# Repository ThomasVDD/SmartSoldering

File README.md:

# SmartSoldering
SmartSoldering - Weller compatible soldering station

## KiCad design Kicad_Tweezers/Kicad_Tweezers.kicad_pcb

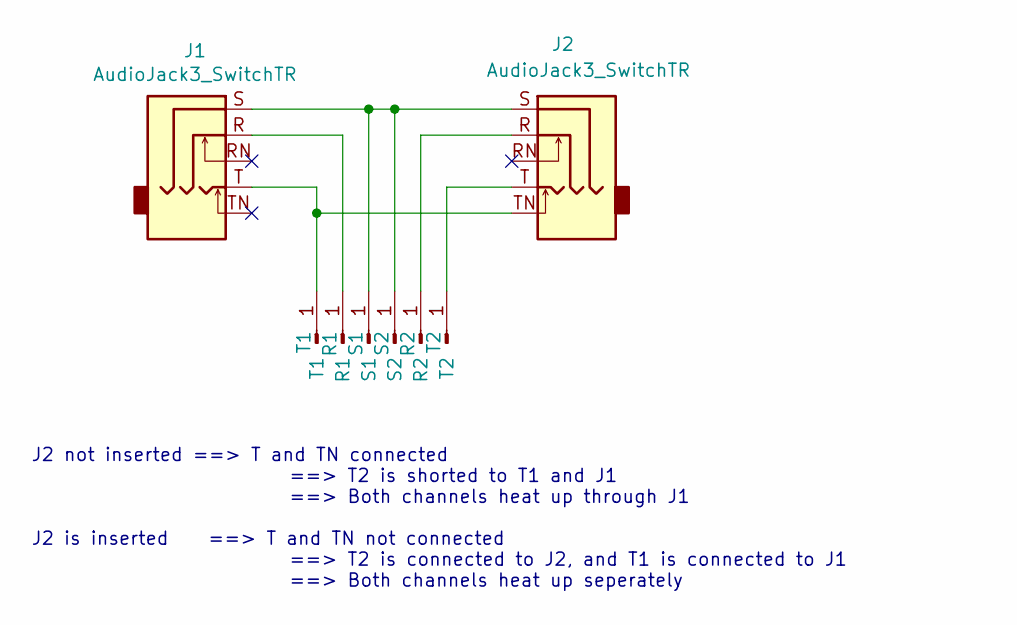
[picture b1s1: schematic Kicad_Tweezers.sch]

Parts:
J1, J2: AudioJack3_SwitchTR; Audiojack3_SwitchTR
R1: R1; Audiojack_pad
R2: R2; Audiojack_pad
S1: S1; Audiojack_pad
S2: S2; Audiojack_pad
T1: T1; Audiojack_pad
T2: T2; Audiojack_pad

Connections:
unnamed: J1.R, R1.1
unnamed: J1.S, J2.S, S1.1, S2.1
unnamed: J1.T, J2.TN, T1.1
unnamed: J2.R, R2.1
unnamed: J2.T, T2.1

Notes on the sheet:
J2 not inserted ==> T and TN connected ==> T2 is shorted to T1 and J1 ==> Both channels heat up through J1 J2 is inserted ==> T and TN not connected ==> T2 is connected to J2, and T1 is connected to J1 ==> Both channels heat up seperately

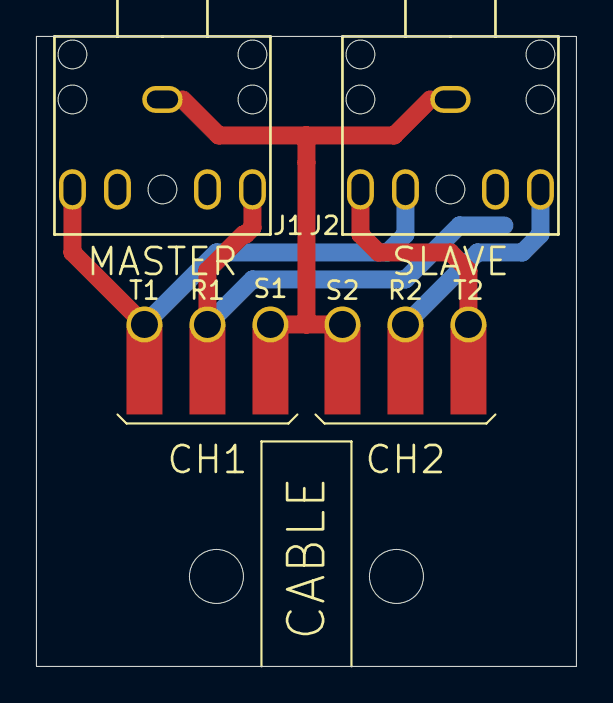
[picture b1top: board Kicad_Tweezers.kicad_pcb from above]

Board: 2 copper layers, 30.0 x 35.0 mm, 8 parts (0 on the bottom side), 5 nets.

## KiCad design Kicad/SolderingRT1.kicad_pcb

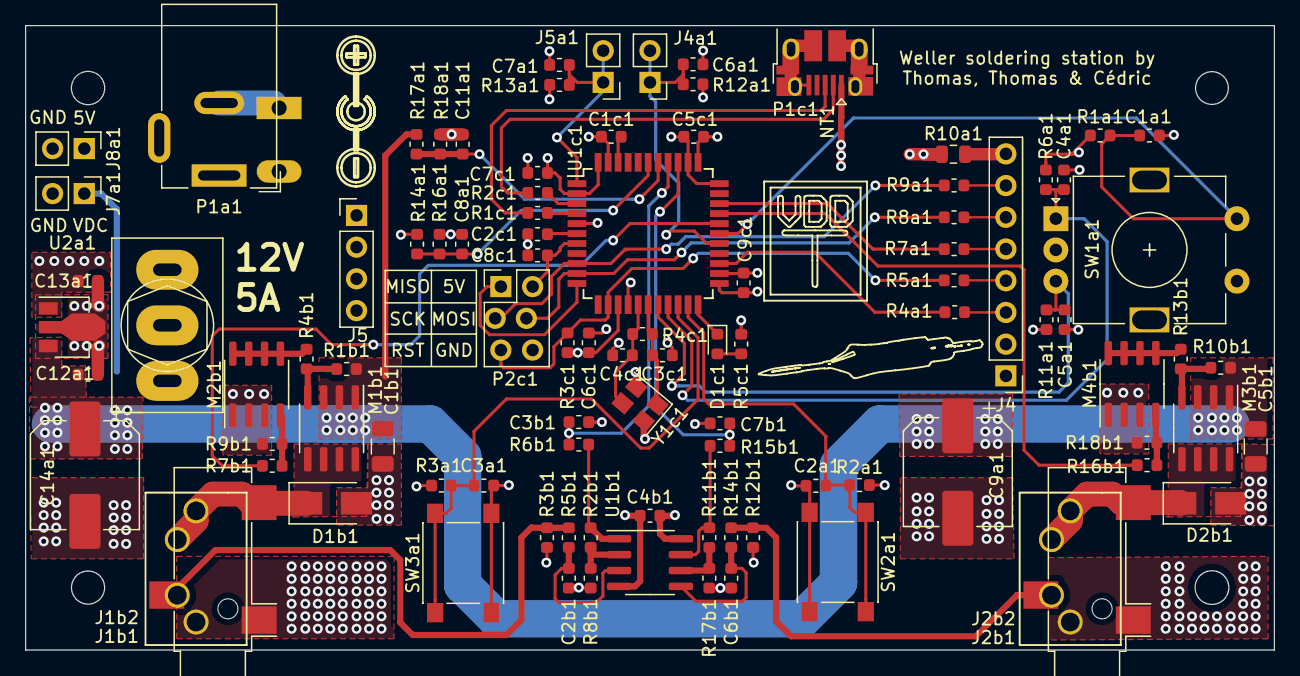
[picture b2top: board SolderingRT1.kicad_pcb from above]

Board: 4 copper layers, 100.0 x 50.0 mm, 99 parts (1 on the bottom side), 56 nets.

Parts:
C1a1, C2a1, C2b1, C3a1, C3b1, C4a1, C5a1, C6a1, C6b1, C7a1, C7b1, C8a1, C11a1: 10nF; C_0603_1608Metric
C1b1, C5b1: 10uF; C_1206_3216Metric
C1c1, C4b1, C5c1, C6c1, C7c1, C8c1, C9c1: 100nF; C_0603_1608Metric
C2c1, C12a1, C13a1: 1uF; C_0603_1608Metric
C3c1, C4c1: 22pF; C_0603_1608Metric
C9a1, C14a1: 330uF; CP_Elec_8x10.5
D1b1, D2b1: SS14; D_SMA
D1c1: LED; LED_0603_1608Metric
J1: Screw_Terminal_01x02; PhoenixContact_MC-G_02x5.08mm_Angled
J1b1, J2b1: AudioJack3; Jack_3.5mm_CUI_SJ-3523-SMT_Horizontal
J1b2, J2b2: AudioJack3; Audiojack_straight
J4: Conn_01x08_Female; PinHeader_1x08_P2.54mm_Vertical
J4a1, J5a1, J7a1, J8a1: Conn_01x02_Male; PinHeader_1x02_P2.54mm_Vertical
J5: Conn_01x04_Female; PinHeader_1x04_P2.54mm_Vertical
M1b1, M3b1: AO4407A; SOIC-8_3.9x4.9mm_P1.27mm
M2b1, M4b1: AOSP36326C; SOIC-8_3.9x4.9mm_P1.27mm
NT1: Net-Tie_2; NetTie-2_SMD_Pad0.5mm
P1a1: Barrel_Jack_Switch; BarrelJack_Wuerth_6941xx301002
P1c1: USB_B_Micro; USB_Micro-B_Amphenol_10103594-0001LF_Horizontal
P2c1: Conn_02x03_Odd_Even; PinHeader_2x03_P2.54mm_Vertical
R1a1, R2a1, R3a1, R3c1, R6a1, R9b1, R11a1, R12a1, R13a1, R17a1, R18b1: 10k; R_0603_1608Metric
R1b1, R5c1, R10b1: 2k4; R_0603_1608Metric
R1c1, R2c1: 22; R_0603_1608Metric
R2b1, R11b1: 56k; R_0603_1608Metric
R3b1, R4c1, R12b1: 1M; R_0603_1608Metric
R4a1, R4b1, R5a1, R5b1, R6b1, R7a1, R7b1, R8a1, R9a1, R13b1, R14b1, R15b1, R16b1, R18a1: 1k; R_0603_1608Metric
R8b1, R17b1: 100; R_0603_1608Metric
R10a1: 150; R_0805_2012Metric
R14a1, R16a1: 100k; R_0603_1608Metric
SW1a1: Rotary_Encoder_Switch; RotaryEncoder_Alps_EC11E-Switch_Vertical_H20mm
SW2a1, SW3a1: SW_Push; SW_Push_1P1T_NO_6x6mm_H9.5mm
SW4a1: SW_SPDT; SW_Toggle_Blue_wSlots
U1b1: OPA2335; SOIC-8_3.9x4.9mm_P1.27mm
U1c1: ATmega32U4-AU; TQFP-44_10x10mm_P0.8mm
U2a1: L78L05_SOT89; SOT-89-3
Y1c1: 16MHz; Crystal_SMD_3225-4Pin_3.2x2.5mm

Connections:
+5V: C4b1.1, C5c1.1, C6c1.1, C7c1.1, C8c1.1, C9c1.1, C13a1.1, J4.1, J8a1.1, NT1.2, P2c1.2, R1a1.2, R2a1.2, R3a1.2, R3b1.2, R3c1.2, R5c1.2, R6a1.2, R10a1.1, R11a1.2, R12a1.2, R12b1.2, R13a1.2, R14a1.2, U1b1.8, U1c1.2, U1c1.7, U1c1.14, U1c1.24, U1c1.34, U1c1.44, U2a1.1
+VDC: C1b1.1, C5b1.1, C9a1.1, C12a1.1, C14a1.1, J7a1.1, M1b1.1, M1b1.2, M1b1.3, M3b1.1, M3b1.2, M3b1.3, R1b1.2, R10b1.2, R17a1.2, SW4a1.3, U2a1.3
/A0-DC: R7a1.1, U1c1.31
/CS: R4a1.1, U1c1.25
/Channels/Temp1: J1b1.R, J1b2.R, R3b1.1, R5b1.2
/Channels/Temp2: J2b1.R, J2b2.R, R12b1.1, R14b1.2
/EncoderA: C4a1.1, R6a1.1, SW1a1.A, U1c1.19
/EncoderB: C5a1.1, R11a1.1, SW1a1.B, U1c1.18
/EncoderSW: C1a1.1, R1a1.1, SW1a1.S2, U1c1.28
/Heater1: R7b1.2, U1c1.29
/Heater2: R16b1.2, U1c1.30
/MOSI-SDA: P2c1.4, R8a1.1, U1c1.10
/Micro/D14-MISO: P2c1.1, U1c1.11
/Micro/GreenLED: D1c1.1, U1c1.22
/NTCtemp1: C8a1.1, R14a1.1, R16a1.1, U1c1.39
/RST: P2c1.5, R3c1.1, R5a1.1, U1c1.13
/RestHeater1: C6a1.1, J4a1.1, J4a1.2, R12a1.1, U1c1.27
/RestHeater2: C7a1.1, J5a1.1, J5a1.2, R13a1.1, U1c1.1
/SCK: P2c1.3, R9a1.1, U1c1.9
/SW1: C2a1.1, R2a1.1, SW2a1.1, U1c1.21
/SW2: C3a1.1, R3a1.1, SW3a1.1, U1c1.20
/Vdcin: C11a1.1, R17a1.1, R18a1.2, U1c1.38
/Vtemp1: C3b1.1, R6b1.1, U1c1.37
/Vtemp2: C7b1.1, R15b1.1, U1c1.36
GND: C1a1.2, C1b1.2, C1c1.2, C2a1.2, C2b1.2, C2c1.2, C3a1.2, C3b1.2, C3c1.1, C4a1.2, C4b1.2, C4c1.1, C5a1.2, C5b1.2, C5c1.2, C6a1.2, C6b1.2, C6c1.2, C7a1.2, C7b1.2, C7c1.2, C8a1.2, C8c1.2, C9a1.2, C9c1.2, C11a1.2, C12a1.2, C13a1.2, C14a1.2, D1b1.2, D2b1.2, J1.1, J1b1.S, J1b2.S, J2b1.S, J2b2.S, J4.2, J7a1.2, J8a1.2, M2b1.1, M2b1.2, M2b1.3, M4b1.1, M4b1.2, M4b1.3, P1a1.2, P1a1.3, P1c1.5, P1c1.6, P2c1.6, R8b1.1, R9b1.1, R16a1.2, R17b1.1, R18a1.1, R18b1.1, SW1a1.C, SW1a1.S1, SW2a1.2, SW3a1.2, U1b1.4, U1c1.5, U1c1.15, U1c1.23, U1c1.33, U1c1.35, U1c1.43, U2a1.2, Y1c1.2, Y1c1.4
unnamed: C1c1.1, U1c1.42
unnamed: C2b1.1, R5b1.1, U1b1.3
unnamed: C2c1.1, U1c1.6
unnamed: C3c1.2, R4c1.2, U1c1.17, Y1c1.1
unnamed: C4c1.2, R4c1.1, U1c1.16, Y1c1.3
unnamed: C6b1.1, R14b1.1, U1b1.5
unnamed: D1b1.1, J1b1.T, J1b2.T, M1b1.5, M1b1.6, M1b1.7, M1b1.8
unnamed: D1c1.2, R5c1.1
unnamed: D2b1.1, J2b1.T, J2b2.T, M3b1.5, M3b1.6, M3b1.7, M3b1.8
unnamed: J1.2, P1a1.1, SW4a1.1, SW4a1.2
unnamed: J4.3, R4a1.2
unnamed: J4.4, R5a1.2
unnamed: J4.5, R7a1.2
unnamed: J4.6, R8a1.2
unnamed: J4.7, R9a1.2
unnamed: J4.8, R10a1.2
unnamed: M1b1.4, R1b1.1, R4b1.2
unnamed: M2b1.4, R7b1.1, R9b1.2
unnamed: M2b1.5, M2b1.6, M2b1.7, M2b1.8, R4b1.1
unnamed: M3b1.4, R10b1.1, R13b1.2
unnamed: M4b1.4, R16b1.1, R18b1.2
unnamed: M4b1.5, M4b1.6, M4b1.7, M4b1.8, R13b1.1
unnamed: NT1.1, P1c1.1
unnamed: P1c1.2, R2c1.1
unnamed: P1c1.3, R1c1.1
unnamed: R1c1.2, U1c1.4
unnamed: R2b1.1, R6b1.2, U1b1.1
unnamed: R2b1.2, R8b1.2, U1b1.2
unnamed: R2c1.2, U1c1.3
unnamed: R11b1.1, R15b1.2, U1b1.7
unnamed: R11b1.2, R17b1.2, U1b1.6

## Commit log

2021-01-05 Added STLs
2021-01-05 Added PCB and Code
